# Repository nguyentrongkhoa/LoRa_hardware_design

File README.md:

# 🌍 Overview

This is a 4-layer RF-LoRa-PCB design for my bachelor thesis. The design entails:

1. LoRa transceiver embedded within the STM32WL55 microcontroller
2. BMV080 sensor and BME680 breakout board from Bosch
3. L80-R GPS module from Quectel to test radio coverage
4. SPV1050 solar energy harvesting module
5. BQ24074 battery charging module with USB-C connector

<table>
  <tr>
    <td></td>
    <td></td>
  </tr>
</table>

<details>
<summary><h1>📋STM32WL55CCU6 pinout configuration</h1>  </summary>

|**Pin number** | **Pin name**| **Description**|
|---------------|--------------------|-----------|
|PA0|Blinky LED|To quick test if flashing works
|PA2|VCP_TX|STLinkV3 virtual com port|
|PA3|VCP_RX|STLinkV3 virtual com port|
|PA4|NSS1|SPI1 slave select|
|PA5|SCK1|SPI1 clock signal|
|PA6|MISO1|SPI1|
|PA7|MOSI1|SPI1|
|PA8|MCO|Hook up to oscilloscope to test TCXO 32MHz output|
|PA9 |TX1|UART to communicate with GPS 
|PA10|RX1|UART to communicate with GPS 
|PA12|GPS_RESET|
|PA13|SWDIO|for flashing/debugging
|PA14|SWDCK|for flashing/debugging
|PB2|ALRT|From MAX17048 fuel gauge when battery is low
|PB3|SWO|for flashing/debugging
|PB6|SCL1|I2C to communicate with gas sensors and fuel gauge
|PB7|SDA1|I2C to communicate with gas sensors and fuel gauge
|PB8 |RF_SW_V2| RF switch control input 2 (to choose between receive and transmit)
|PB12|RF_SW_V1| RF switch control input 1
</details>

<details>
  
<summary><h1>🔌Testpoints setup</h1> </summary>

|**Testpoint name** | **Description**| **Expected result**
|---------------|--------------------|----------|
|VBUS|USB voltage|5V when USB is connected
|OUT|output of BQ24074 battery charging module|4.2V when battery is full, ~3.5V when battery empty
|ALRT|MAX17048 fuel gauge alert signal when battery is low|3.3V when battery is full, 0V when empty 

</details>

<details>
<summary><h1>🔍PCB inspection result</h1></summary>
  
## Detailed testing
### Visual inspection
### Electrical tests

#### Power consumption 

</details>

<details>
<summary><h1>✅<b>TODOs for next version</b></h1></summary>

- [ ] Replace SMA connector from Samtec with a cheaper one (see notes in schematic)
- [ ] Tune the antenna side matching network with NanoVNA
- [ ] Remove GPS module since TTFF (time-to-first-fix) is too long
- [ ] Move BMV080 away from MCU
- [ ] Fix VCP (virtual COM port) connections so that debug prints can be displayed in the host comp's terminal
- [ ] Fix PCB edge cut so that it's rectangular and not jagged
- [ ] Fix BMV080 orientation (so that it does not overlap solar cell)
- [ ] Remove USB charging (including BQ24072 charging IC), since the 3.3V LDO of the SPV1050 with max 200 mA can supply the       whole system

</details>

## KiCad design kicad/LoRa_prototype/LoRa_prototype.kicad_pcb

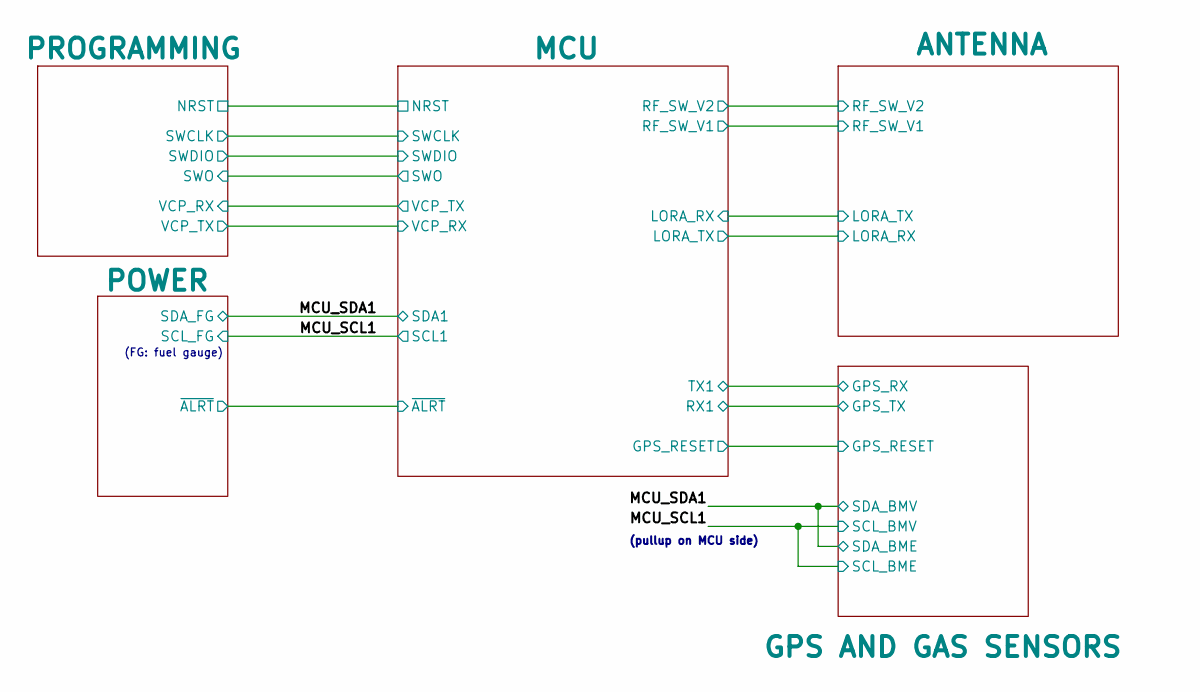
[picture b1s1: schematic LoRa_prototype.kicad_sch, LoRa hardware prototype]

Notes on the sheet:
(FG: fuel gauge)
(pullup on MCU side)

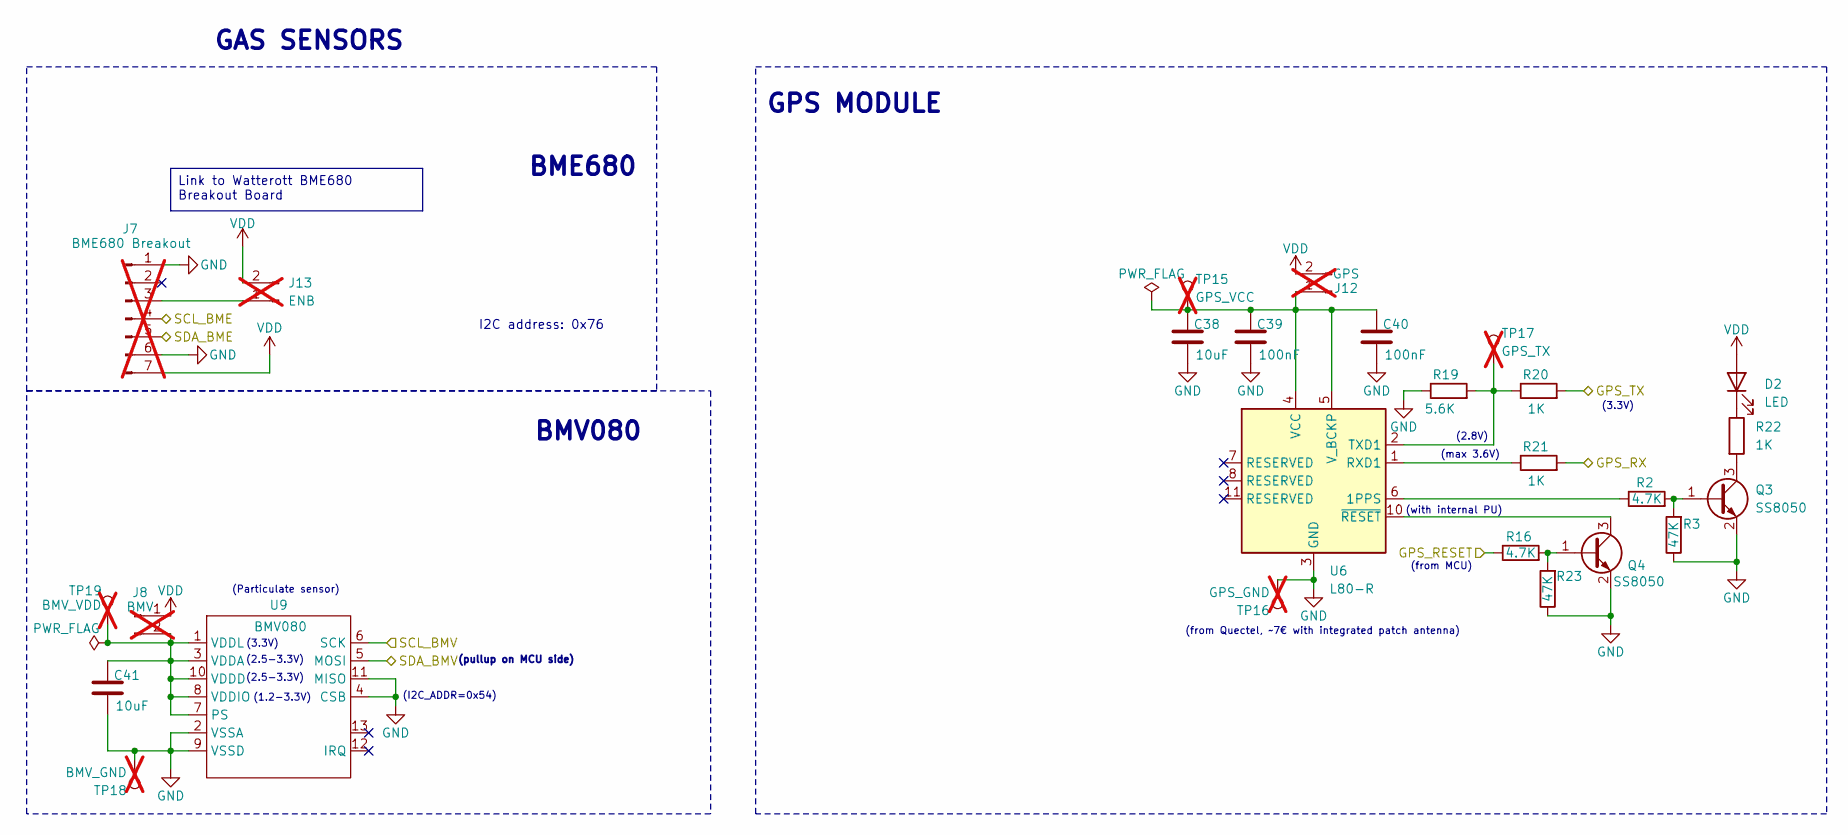
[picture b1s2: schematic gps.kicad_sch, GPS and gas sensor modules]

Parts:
C38, C41: 10uF; C_0603_1608Metric
C39: 100nF; C_0402_1005Metric
C40: 100nF; C_0603_1608Metric
D2: LED; LED_0805_2012Metric
J7: BME680 Breakout; PinSocket_1x07_P2.54mm_Vertical; not fitted
J8: BMV; PinHeader_1x02_P2.54mm_Vertical; not fitted
J12: GPS; PinHeader_1x02_P2.54mm_Vertical; not fitted
J13: ENB; PinHeader_1x02_P2.54mm_Vertical; not fitted
Q3, Q4: SS8050; SOT-23
R2, R16: 4.7K; R_0805_2012Metric
R3, R23: 47K; R_0805_2012Metric
R19: 5.6K; R_0805_2012Metric
R20, R21, R22: 1K; R_0805_2012Metric
TP15: GPS_VCC; TestPoint_Pad_2.0x2.0mm; not fitted
TP16: GPS_GND; TestPoint_Pad_2.0x2.0mm; not fitted
TP17: GPS_TX; TestPoint_Pad_2.0x2.0mm; not fitted
TP18: BMV_GND; TestPoint_Pad_2.0x2.0mm; not fitted
TP19: BMV_VDD; TestPoint_Pad_2.0x2.0mm; not fitted
U6: L80-R; Quectel_L80-R
U9: BMV080; CON_5035661302_MOL; LCSC C587979

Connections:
/GPS AND GAS SENSORS/GPS_RESET: R16.1; also elsewhere on the board
/MCU/RX1: R20.2; also elsewhere on the board
/MCU/TX1: R21.2; also elsewhere on the board
/MCU_SCL1: J7.4, U9.6 (SCK); also elsewhere on the board
/MCU_SDA1: J7.5, U9.5 (MOSI); also elsewhere on the board
GND: C38.2, C39.2, C40.2, C41.2, J7.1, J7.6, Q3.2 (E), Q4.2 (E), R3.1, R19.1, R23.1, TP16.1 (1_1), TP18.1 (1_1), U6.3 (GND), U6.12 (GND), U9.2 (VSSA), U9.4 (CSB), U9.9 (VSSD), U9.11 (MISO); also elsewhere on the board
unnamed: D2.1 (K), R22.1
unnamed: C41.1, J8.2, TP19.1 (1_1), U9.1 (VDDL), U9.3 (VDDA), U9.7 (PS), U9.8 (VDDIO), U9.10 (VDDD)
unnamed: C38.1, C39.1, C40.1, J12.1, TP15.1 (1_1), U6.4 (VCC), U6.5 (V_BCKP)
unnamed: J7.3, J13.1
unnamed: Q3.1 (B), R2.2, R3.2
unnamed: Q3.3 (C), R22.2
unnamed: Q4.1 (B), R16.2, R23.2
unnamed: Q4.3 (C), U6.10 (~RESET)
unnamed: R2.1, U6.6 (1PPS)
unnamed: R21.1, U6.1 (RXD1)
unnamed: R19.2, R20.1, TP17.1 (1_1), U6.2 (TXD1)
VDD: D2.2 (A), J7.7, J8.1, J12.2, J13.2; also elsewhere on the board

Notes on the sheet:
BME680
(from MCU)
BMV080
(max 3.6V)
(with internal PU)
(I2C_ADDR=0x54)
(2.8V)
(from Quectel, ~7€ with integrated patch antenna)
GPS MODULE
(Particulate sensor)
GAS SENSORS
(3.3V)
(pullup on MCU side)
(2.5-3.3V)
I2C address: 0x76
(1.2-3.3V)
Link to Watterott BME680 Breakout Board

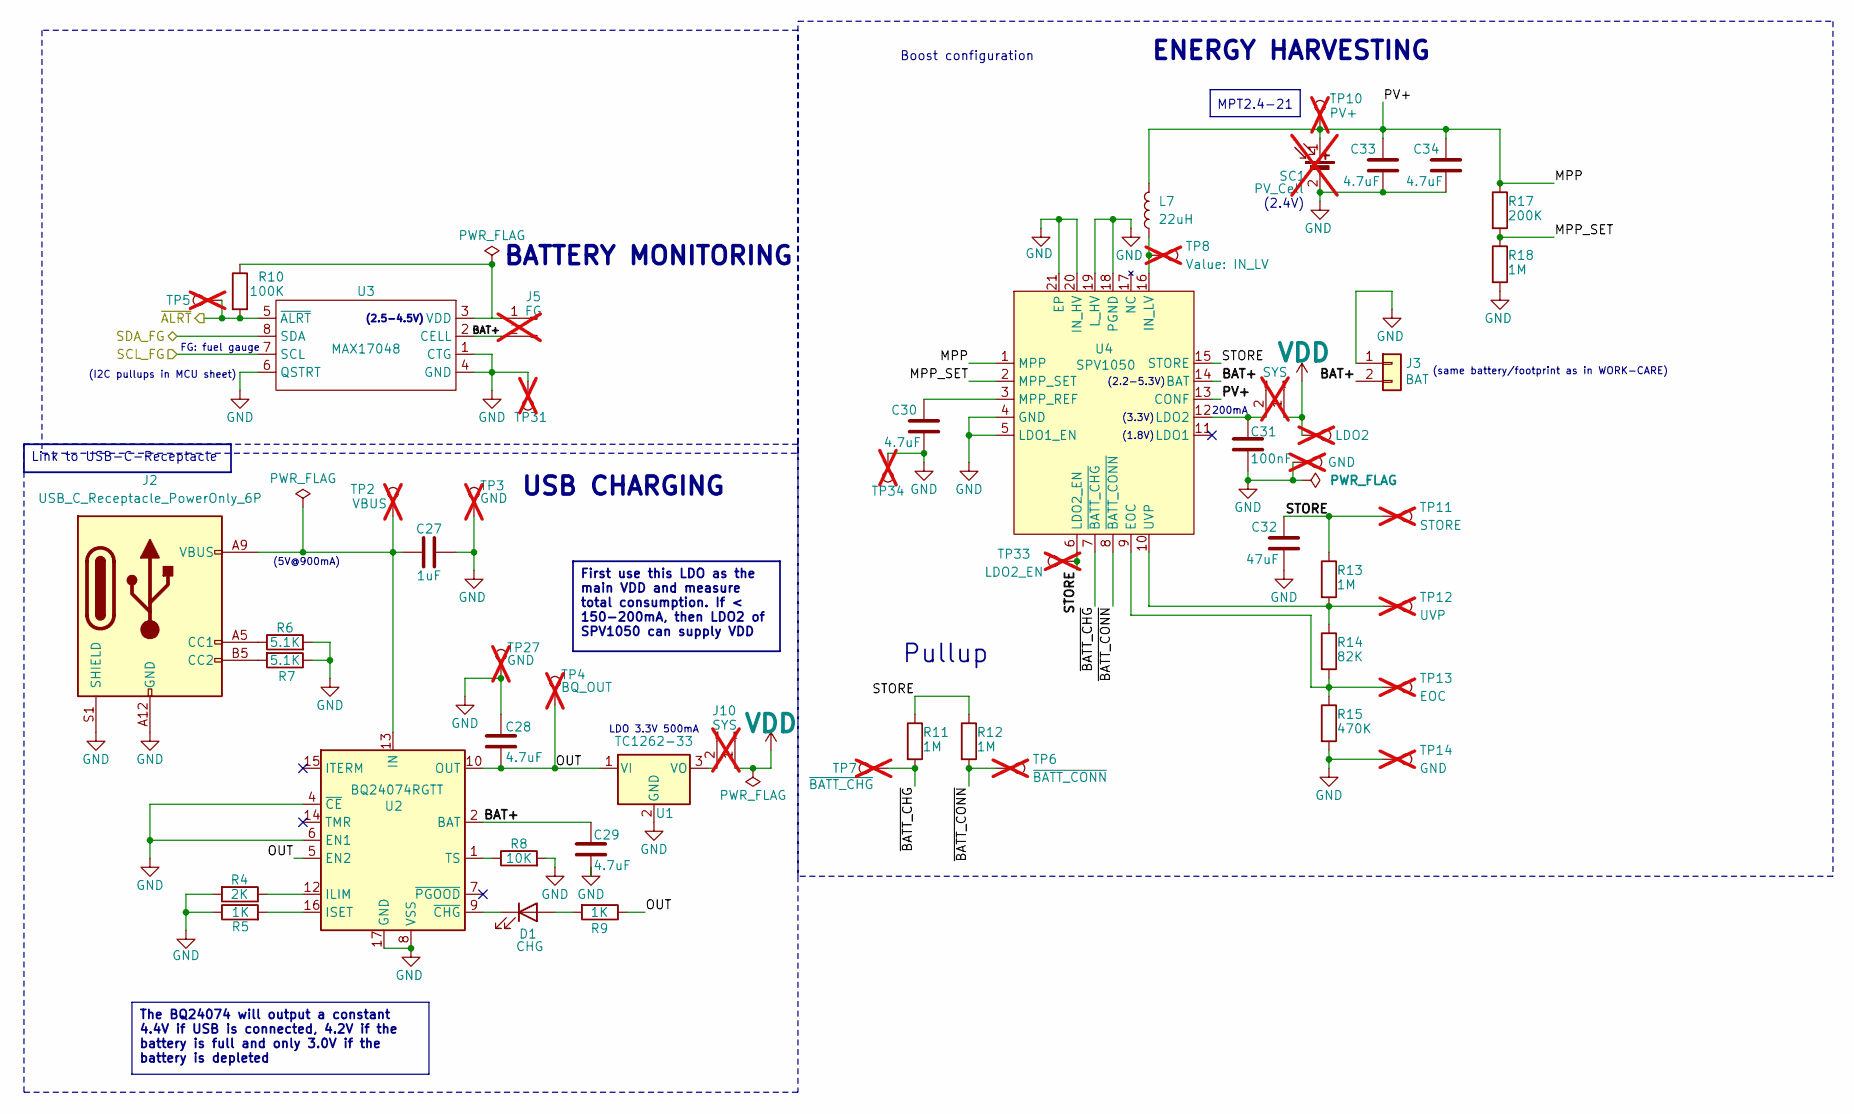
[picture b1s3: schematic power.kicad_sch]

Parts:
C27: 1uF; C_0603_1608Metric; LCSC C1592
C28, C29: 4.7uF; C_0603_1608Metric; LCSC C19666
C30, C33, C34: 4.7uF; C_0603_1608Metric
C31: 100nF; C_0402_1005Metric
C32: 47uF; C_0805_2012Metric
D1: CHG; LED_0805_2012Metric; LCSC C94740
J2: USB_C_Receptacle_PowerOnly_6P; UC17-0B06F68011
J3: BAT; JST_GH_SM02B-GHS-TB_1x02-1MP_P1.25mm_Horizontal; LCSC C189893
J5: FG; PinHeader_1x02_P2.54mm_Vertical; not fitted
J10, J15: SYS; PinHeader_1x02_P2.54mm_Vertical; not fitted
L7: 22uH; PSPMAA0402-220M-ANP
R4: 2K; R_0805_2012Metric; LCSC C4177
R5: 1K; R_0805_2012Metric; LCSC C21190
R6, R7: 5.1K; R_0805_2012Metric
R8: 10K; R_0805_2012Metric; LCSC C25804
R9: 1K; R_0805_2012Metric; LCSC C20686
R10: 100K; R_0805_2012Metric
R11, R12, R13, R18: 1M; R_0805_2012Metric
R14: 82K; R_0603_1608Metric
R15: 470K; R_0805_2012Metric
R17: 200K; R_0805_2012Metric
SC1: PV_Cell; MPT2.4-21; not fitted
TP2: VBUS; TestPoint_Pad_2.0x2.0mm; not fitted
TP3, TP14, TP27, TP28, TP31, TP34: GND; TestPoint_Pad_2.0x2.0mm; not fitted
TP4: BQ_OUT; TestPoint_Pad_2.0x2.0mm; not fitted
TP5: ~{ALRT}; TestPoint_Pad_2.0x2.0mm; not fitted
TP6: ~{BATT_CONN}; TestPoint_Pad_2.0x2.0mm; not fitted
TP7: ~{BATT_CHG}; TestPoint_Pad_2.0x2.0mm; not fitted
TP8: IN_LV; TestPoint_Pad_2.0x2.0mm; not fitted
TP9: LDO2; TestPoint_Pad_2.0x2.0mm; not fitted
TP10: PV+; TestPoint_Pad_2.0x2.0mm; not fitted
TP11: STORE; TestPoint_Pad_2.0x2.0mm; not fitted
TP12: UVP; TestPoint_Pad_2.0x2.0mm; not fitted
TP13: EOC; TestPoint_Pad_2.0x2.0mm; not fitted
TP33: LDO2_EN; TestPoint_Pad_2.0x2.0mm; not fitted
U1: TC1262-33; SOT-223-3
U2: BQ24074RGTT; VQFN-16-1EP_3x3mm_P0.5mm_EP1.6x1.6mm; LCSC C54313
U3: MAX17048; SON50P200X200X80-9N
U4: SPV1050; QFN40P300X300X100-21N

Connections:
/MCU/~ALRT: R10.2, TP5.1 (1_1), U3.5 (~ALRT); also elsewhere on the board
/MCU_SCL1: U3.7 (SCL); also elsewhere on the board
/MCU_SDA1: U3.8 (SDA); also elsewhere on the board
/POWER/BAT+: C29.2, J3.2, J5.2, U2.2 (BAT), U2.3 (BAT), U3.2 (CELL), U4.14 (BAT)
/POWER/MPP: C33.2, C34.2, L7.2, R17.1, SC1.1 (+), TP10.1 (1_1), U4.1 (MPP), U4.13 (CONF)
/POWER/MPP_SET: R17.2, R18.1, U4.2 (MPP_SET)
/POWER/OUT: C28.1, R9.1, TP4.1 (1_1), U1.1 (VI), U2.5 (EN2), U2.10 (OUT), U2.11 (OUT)
/POWER/STORE: C32.2, R11.1, R12.1, R13.1, TP11.1 (1_1), TP33.1 (1_1), U4.6 (LDO2_EN), U4.15 (STORE); also elsewhere on the board
/POWER/~BATT_CHG: R11.2, TP7.1 (1_1), U4.7 (~BATT_CHG)
/POWER/~BATT_CONN: R12.2, TP6.1 (1_1), U4.8 (~BATT_CONN)
GND: C27.2, C28.2, C29.1, C30.1, C31.2, C32.1, C33.1, C34.1, J2.A12 (GND), J2.B12 (GND), J2.S1 (SHIELD), J3.1, R4.2, R5.1, R6.2, R7.1, R8.2, R15.2, R18.2, SC1.2 (-), TP3.1 (1_1), TP14.1 (1_1), TP27.1 (1_1), TP28.1 (1_1), TP31.1 (1_1), TP34.1 (1_1), U1.2 (GND), U2.4 (~CE), U2.6 (EN1), U2.8 (VSS), U2.17 (GND), U3.1 (CTG), U3.4 (GND), U3.6 (QSTRT), U4.4 (GND), U4.5 (LDO1_EN), U4.18 (PGND), U4.19 (L_HV), U4.20 (IN_HV), U4.21 (EP); also elsewhere on the board
unnamed: D1.2 (A), R9.2
unnamed: D1.1 (K), U2.9 (~CHG)
unnamed: J2.A5 (CC1), R6.1
unnamed: J2.B5 (CC2), R7.2
unnamed: J5.1, R10.1, U3.3 (VDD)
unnamed: J10.2, U1.3 (VO)
unnamed: C31.1, J15.2, U4.12 (LDO2)
unnamed: R4.1, U2.12 (ILIM)
unnamed: C27.1, J2.A9 (VBUS), J2.B9 (VBUS), TP2.1 (1_1), U2.13 (IN)
unnamed: R5.2, U2.16 (ISET)
unnamed: R8.1, U2.1 (TS)
unnamed: R14.2, R15.1, TP13.1 (1_1), U4.9 (EOC)
unnamed: L7.1, TP8.1 (1_1), U4.16 (IN_LV)
unnamed: C30.2, U4.3 (MPP_REF)
unnamed: R13.2, R14.1, TP12.1 (1_1), U4.10 (UVP)
VDD: J10.1, J15.1, TP9.1 (1_1); also elsewhere on the board

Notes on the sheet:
Boost configuration
(5V@900mA)
ENERGY HARVESTING
(2.5-4.5V)
200mA
BATTERY MONITORING
MPT2.4-21
(2.2-5.3V)
FG: fuel gauge
(3.3V)
LDO 3.3V 500mA
Pullup
USB CHARGING
(same battery/footprint as in WORK-CARE)
(2.4V)
(I2C pullups in MCU sheet)
(1.8V)
Link to USB-C-Receptacle
First use this LDO as the main VDD and measure total consumption. If < 150-200mA, then LDO2 of SPV1050 can supply VDD
The BQ24074 will output a constant 4.4V if USB is connected, 4.2V if the battery is full and only 3.0V if the battery is depleted

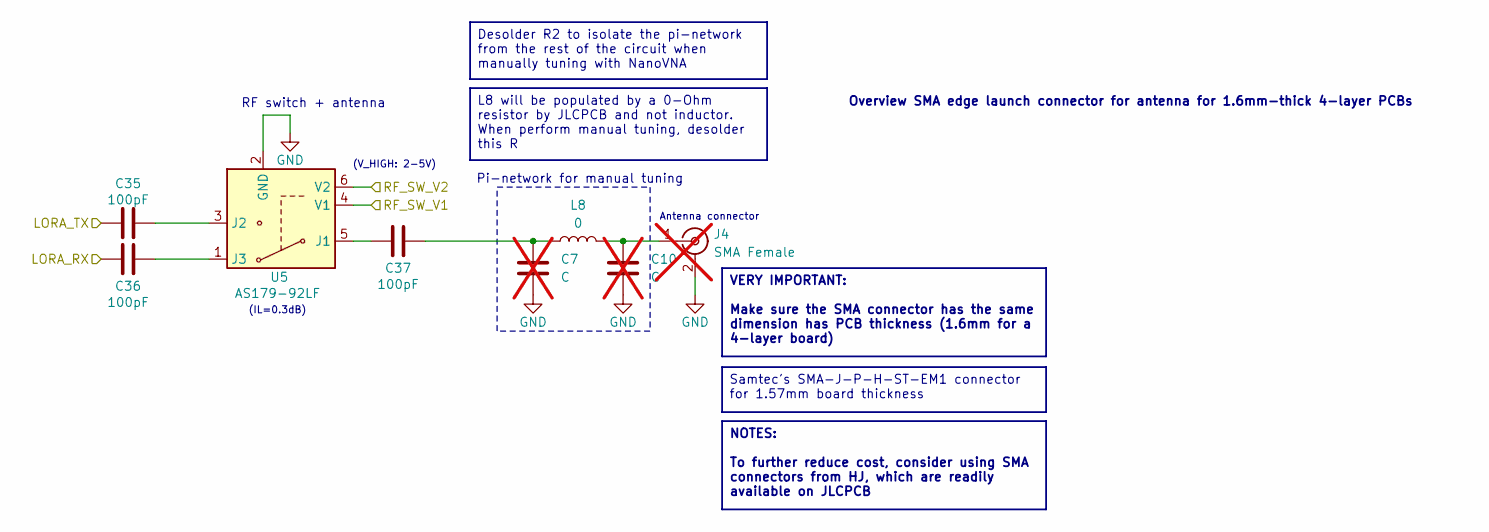
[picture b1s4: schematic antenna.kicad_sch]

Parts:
C7, C10: C; C_0603_1608Metric; not fitted
C35, C36, C37: 100pF; C_0402_1005Metric
J4: SMA Female; SMA_Samtec_SMA-J-P-H-ST-EM1_EdgeMount; LCSC C5137195; not fitted
L8: 0; L_0603_1608Metric
U5: AS179-92LF; SOT-363_SC-70-6

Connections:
/ANTENNA/LORA_RX: C36.1; also elsewhere on the board
/ANTENNA/LORA_TX: C35.1; also elsewhere on the board
/ANTENNA/RF_SW_V1: U5.4 (V1); also elsewhere on the board
/ANTENNA/RF_SW_V2: U5.6 (V2); also elsewhere on the board
GND: C7.2, C10.2, J4.2 (Ext), U5.2 (GND); also elsewhere on the board
unnamed: C7.1, C37.2, L8.1
unnamed: C10.1, J4.1 (In), L8.2
unnamed: C37.1, U5.5 (J1)
unnamed: C35.2, U5.3 (J2)
unnamed: C36.2, U5.1 (J3)

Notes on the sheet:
(V_HIGH: 2-5V)
Pi-network for manual tuning
RF switch + antenna
(IL=0.3dB)
Antenna connector
Overview SMA edge launch connector for antenna for 1.6mm-thick 4-layer PCBs
Samtec's SMA-J-P-H-ST-EM1 connector for 1.57mm board thickness
Desolder R2 to isolate the pi-network from the rest of the circuit when manually tuning with NanoVNA
L8 will be populated by a 0-Ohm resistor by JLCPCB and not inductor. When perform manual tuning, desolder this R
VERY IMPORTANT: Make sure the SMA connector has the same dimension has PCB thickness (1.6mm for a 4-layer board)
NOTES: To further reduce cost, consider using SMA connectors from HJ, which are readily available on JLCPCB

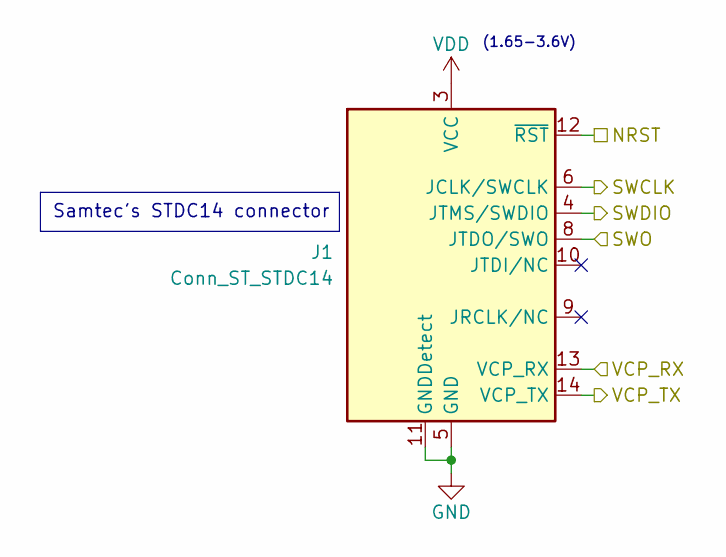
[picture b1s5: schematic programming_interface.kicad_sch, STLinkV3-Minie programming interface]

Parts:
J1: Conn_ST_STDC14; PinHeader_2x07_P1.27mm_Vertical

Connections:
/MCU/NRST: J1.12 (~RST); also elsewhere on the board
/MCU/SWCLK: J1.6 (JCLK/SWCLK); also elsewhere on the board
/MCU/SWDIO: J1.4 (JTMS/SWDIO); also elsewhere on the board
/MCU/SWO: J1.8 (JTDO/SWO); also elsewhere on the board
/MCU/VCP_RX: J1.14 (VCP_TX); also elsewhere on the board
/MCU/VCP_TX: J1.13 (VCP_RX); also elsewhere on the board
GND: J1.5 (GND), J1.7 (GND), J1.11 (GNDDetect); also elsewhere on the board
VDD: J1.3 (VCC); also elsewhere on the board

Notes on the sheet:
Samtec's STDC14 connector
(1.65-3.6V)

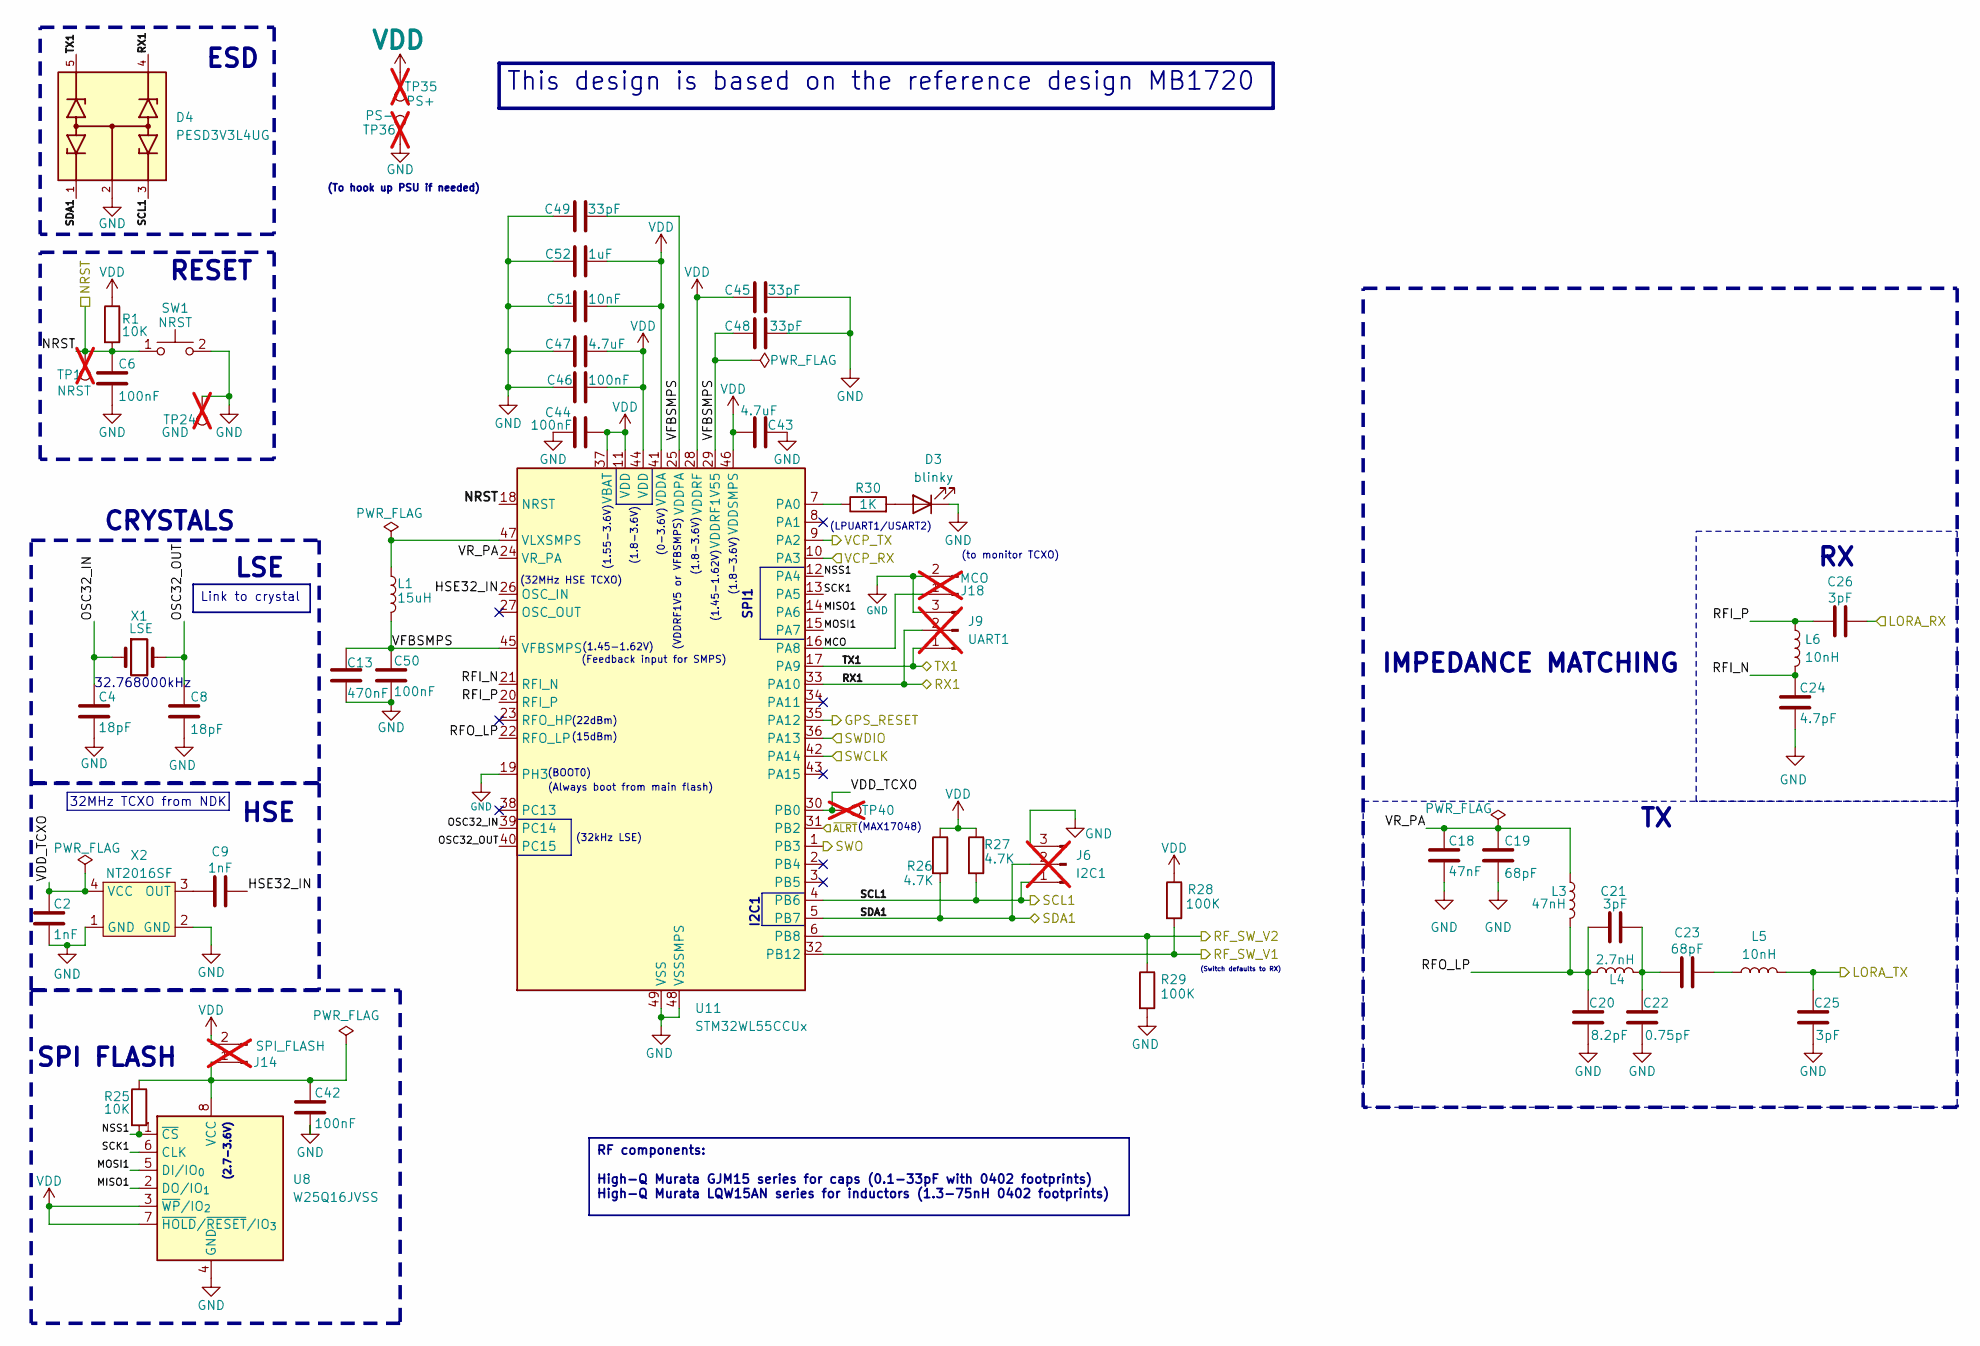
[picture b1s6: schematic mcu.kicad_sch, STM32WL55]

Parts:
C2, C9: 1nF; C_0402_1005Metric
C4, C8: 18pF; C_0402_1005Metric
C6, C42, C44, C46, C50: 100nF; C_0402_1005Metric
C13: 470nF; C_0603_1608Metric
C18: 47nF; C_0603_1608Metric
C19, C23: 68pF; C_0402_1005Metric
C20: 8.2pF; C_0402_1005Metric
C21, C25, C26: 3pF; C_0402_1005Metric
C22: 0.75pF; C_0402_1005Metric
C24: 4.7pF; C_0402_1005Metric
C43, C47: 4.7uF; C_0402_1005Metric
C45, C48, C49: 33pF; C_0402_1005Metric
C51: 10nF; C_0402_1005Metric
C52: 1uF; C_0402_1005Metric
D3: blinky; LED_0805_2012Metric
D4: PESD3V3L4UG; DIO_PESD3V3L4UG; PARTREV 04
J6: I2C1; PinHeader_1x03_P2.54mm_Vertical; not fitted
J9: UART1; PinHeader_1x03_P2.54mm_Vertical; not fitted
J14: SPI_FLASH; PinHeader_1x02_P2.54mm_Vertical; not fitted
J18: MCO; PinHeader_1x02_P2.54mm_Vertical; not fitted
L1: 15uH; L_0402_1005Metric
L3: 47nH; L_0402_1005Metric
L4: 2.7nH; L_0402_1005Metric
L5, L6: 10nH; L_0402_1005Metric
R1: 10K; R_0603_1608Metric
R25: 10K; R_0805_2012Metric
R26, R27: 4.7K; R_0603_1608Metric
R28, R29: 100K; R_0603_1608Metric
R30: 1K; R_0603_1608Metric
SW1: NRST; TS-1088-AR02016
TP1: NRST; TestPoint_Pad_2.0x2.0mm; not fitted
TP24: GND; TestPoint_Pad_2.0x2.0mm; not fitted
TP35: PS+; TestPoint_THTPad_2.0x2.0mm_Drill1.0mm; not fitted
TP36: PS-; TestPoint_THTPad_2.0x2.0mm_Drill1.0mm; not fitted
TP40: VDDXO; TestPoint_Pad_2.0x2.0mm; not fitted
U8: W25Q16JVSS; SOIC-8_5.3x5.3mm_P1.27mm
U11: STM32WL55CCUx; QFN-48-1EP_7x7mm_P0.5mm_EP5.6x5.6mm
X1: LSE; Crystal_SMD_3215-2Pin_3.2x1.5mm
X2: NT2016SF; NT2016SF TCXO

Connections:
/ANTENNA/LORA_RX: C25.1, L5.2; also elsewhere on the board
/ANTENNA/LORA_TX: C26.2; also elsewhere on the board
/ANTENNA/RF_SW_V1: R28.2, U11.32 (PB12); also elsewhere on the board
/ANTENNA/RF_SW_V2: R29.1, U11.6 (PB8); also elsewhere on the board
/GPS AND GAS SENSORS/GPS_RESET: U11.35 (PA12); also elsewhere on the board
/MCU/HSE32_IN: C9.2, U11.26 (OSC_IN)
/MCU/MCO: J18.1, U11.16 (PA8)
/MCU/MISO1: U8.2 (DO/IO_{1}), U11.14 (PA6)
/MCU/MOSI1: U8.5 (DI/IO_{0}), U11.15 (PA7)
/MCU/NRST: C6.1, R1.2, SW1.1, TP1.1 (1_1), U11.18 (NRST); also elsewhere on the board
/MCU/NSS1: R25.2, U8.1 (~CS), U11.12 (PA4)
/MCU/OSC32_IN: C4.1, U11.39 (PC14), X1.1
/MCU/OSC32_OUT: C8.1, U11.40 (PC15), X1.2
/MCU/RFI_N: C24.1, L6.2, U11.21 (RFI_N)
/MCU/RFI_P: C26.1, L6.1, U11.20 (RFI_P)
/MCU/RFO_LP: C20.1, C21.1, L3.2, L4.1, U11.22 (RFO_LP)
/MCU/RX1: D4.4, J9.2, U11.33 (PA10); also elsewhere on the board
/MCU/SCK1: U8.6 (CLK), U11.13 (PA5)
/MCU/SWCLK: U11.42 (PA14); also elsewhere on the board
/MCU/SWDIO: U11.36 (PA13); also elsewhere on the board
/MCU/SWO: U11.1 (PB3); also elsewhere on the board
/MCU/TX1: D4.5, J9.1, U11.17 (PA9); also elsewhere on the board
/MCU/VCP_RX: U11.10 (PA3); also elsewhere on the board
/MCU/VCP_TX: U11.9 (PA2); also elsewhere on the board
/MCU/VDD_TCXO: C2.1, TP40.1 (1_1), U11.30 (PB0), X2.4 (VCC)
/MCU/VFBSMPS: C13.1, C48.1, C49.2, C50.1, L1.2, U11.25 (VDDPA), U11.29 (VDDRF1V55), U11.45 (VFBSMPS)
/MCU/VR_PA: C18.1, C19.1, L3.1, U11.24 (VR_PA)
/MCU/~ALRT: U11.31 (PB2); also elsewhere on the board
/MCU_SCL1: D4.3, J6.1, R27.2, U11.4 (PB6); also elsewhere on the board
/MCU_SDA1: D4.1, J6.2, R26.2, U11.5 (PB7); also elsewhere on the board
GND: C2.2, C4.2, C6.2, C8.2, C13.2, C18.2, C19.2, C20.2, C22.2, C24.2, C25.2, C42.2, C43.2, C44.2, C45.2, C46.2, C47.2, C48.2, C49.1, C50.2, C51.2, C52.2, D3.1 (K), D4.2, J6.3, J9.3, J18.2, R29.2, SW1.2, TP24.1 (1_1), TP36.1 (1_1), U8.4 (GND), U11.19 (PH3), U11.48 (VSSSMPS), U11.49 (VSS), X2.1 (GND), X2.2 (GND); also elsewhere on the board
unnamed: C21.2, C22.1, C23.1, L4.2
unnamed: C23.2, L5.1
unnamed: D3.2 (A), R30.2
unnamed: C42.1, J14.1, R25.1, U8.8 (VCC)
unnamed: R30.1, U11.7 (PA0)
unnamed: L1.1, U11.47 (VLXSMPS)
unnamed: C9.1, X2.3 (OUT)
VDD: C43.1, C44.1, C45.1, C46.1, C47.1, C51.1, C52.1, J14.2, R1.1, R26.1, R27.1, R28.1, TP35.1 (1_1), U8.3 (~WP/IO_{2}), U8.7 (~HOLD/~RESET/IO_{3}), U11.11 (VDD), U11.28 (VDDRF), U11.37 (VBAT), U11.41 (VDDA), U11.44 (VDD), U11.46 (VDDSMPS); also elsewhere on the board

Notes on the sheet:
SPI FLASH
RESET
IMPEDANCE MATCHING
(1.45-1.62V)
(To hook up PSU if needed)
(LPUART1/USART2)
(1.8-3.6V)
(BOOT0)
(Feedback input for SMPS)
I2C1
(0-3.6V)
(32kHz LSE)
(MAX17048)
CRYSTALS
(Switch defaults to RX)
LSE
(15dBm)
(2.7-3.6V)
32MHz TCXO from NDK
SPI1
(32MHz HSE TCXO)
ESD
(1.55-3.6V)
HSE
(to monitor TCXO)
(22dBm)
(VDDRF1V5 or VFBSMPS)
32.768000kHz
(Always boot from main flash)
RF components: High-Q Murata GJM15 series for caps (0.1-33pF with 0402 footprints) High-Q Murata LQW15AN series for inductors (1.3-75nH 0402 footprints)
This design is based on the reference design MB1720
Link to crystal

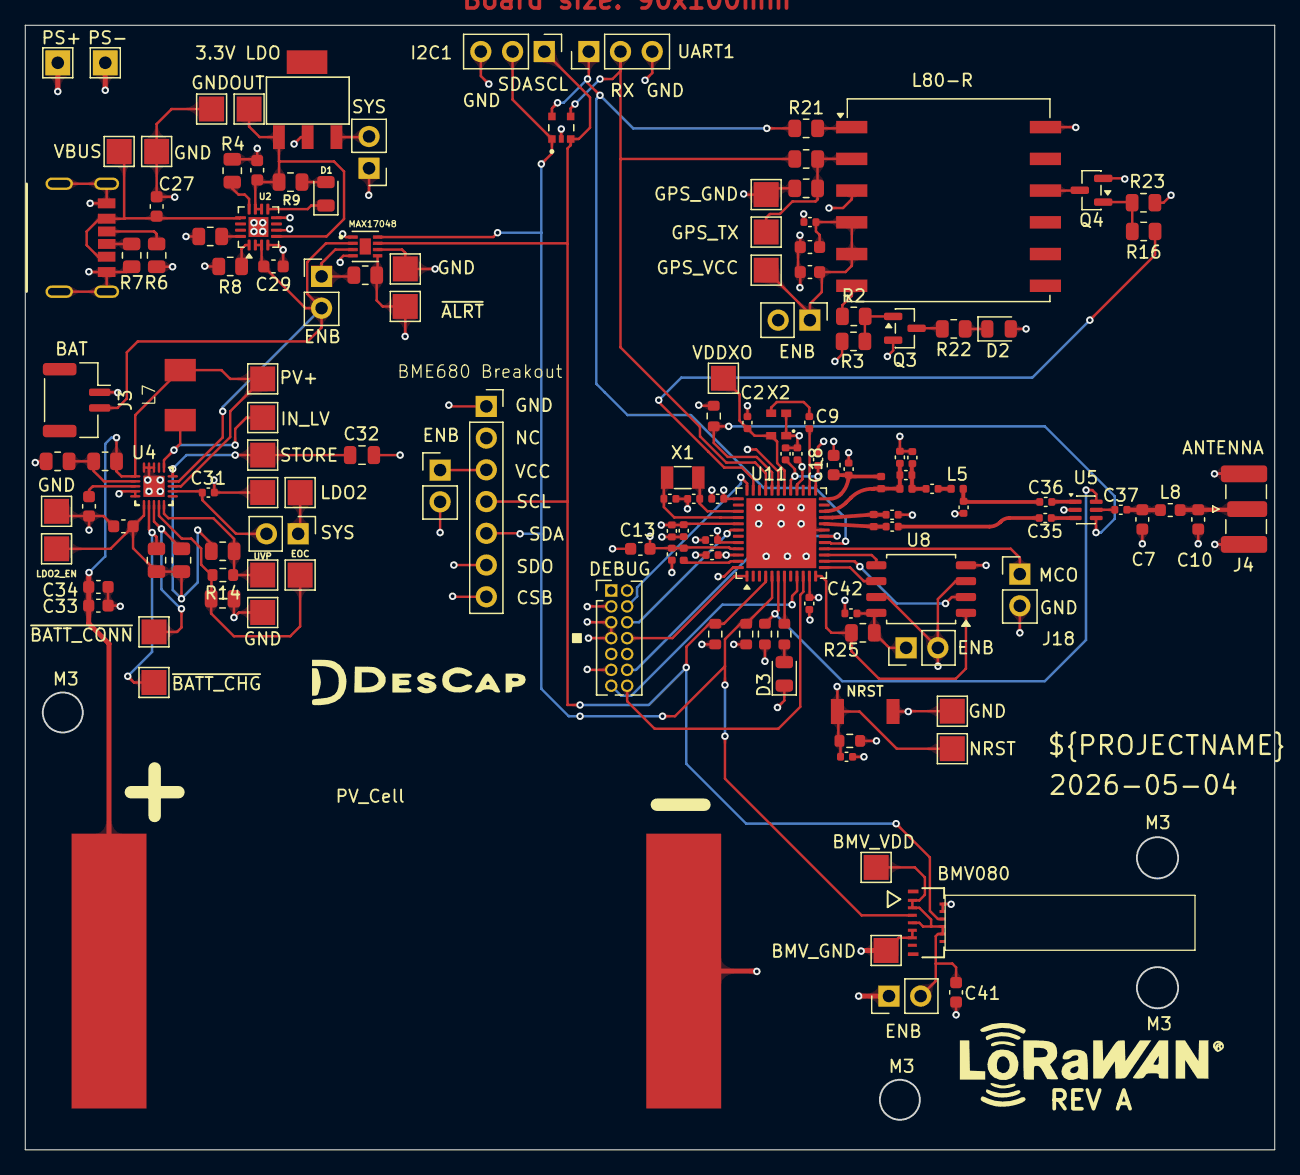
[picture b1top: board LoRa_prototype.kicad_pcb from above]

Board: 4 copper layers, 99.9 x 89.9 mm, 142 parts (0 on the bottom side), 77 nets.

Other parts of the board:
C32#2: 47uF; C_0805_2012Metric

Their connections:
/POWER/STORE: C32#2.2; also elsewhere on the board
GND: C32#2.1; also elsewhere on the board

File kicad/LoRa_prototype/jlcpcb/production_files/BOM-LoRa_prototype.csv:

Comment,Designator,Footprint,LCSC,Quantity
0,L8,L_0603_1608Metric,C21189,1
0.75pF,C22,C_0402_1005Metric,C2931057,1
1.5M,R17,R_0805_2012Metric,C26110,1
1.8K,R4,R_0805_2012Metric,C17420,1
100K,R10,R_0805_2012Metric,C149504,1
100K,"R28,R29",R_0603_1608Metric,C25803,2
100nF,C40,C_0603_1608Metric,C14663,1
100nF,"C31,C39,C42,C44,C46,C50,C6",C_0402_1005Metric,C1525,7
100pF,"C35,C36,C37",C_0402_1005Metric,C77177,3
10K,"R25,R8",R_0805_2012Metric,C17414,2
10K,R1,R_0603_1608Metric,C25804,1
10M,"R11,R12",R_0805_2012Metric,C101929,2
10nF,C51,C_0402_1005Metric,C15195,1
10nH,"L5,L6",L_0402_1005Metric,C184029,2
10uF,"C38,C41",C_0603_1608Metric,C19702,2
15uH,L1,L_0402_1005Metric,C3221788,1
18pF,"C4,C8",C_0402_1005Metric,C1549,2
1K,"R20,R21,R22,R5,R9",R_0805_2012Metric,C17513,5
1K,R30,R_0603_1608Metric,C21190,1
1nF,"C2,C9",C_0402_1005Metric,C1523,2
1uF,C27,C_0603_1608Metric,C15849,1
1uF,C52,C_0402_1005Metric,C52923,1
2.7M,R15,R_0805_2012Metric,C170861,1
2.7nH,L4,L_0402_1005Metric,C91239,1
22uH,L7,L_0402_1005Metric,C5273842,1
3.6nH,L2,L_0402_1005Metric,C408158,1
33pF,"C45,C48,C49",C_0402_1005Metric,C76905,3
3pF,"C21,C25,C26",C_0402_1005Metric,C76906,3
4.7K,"R26,R27",R_0603_1608Metric,C23162,2
4.7pF,C24,C_0402_1005Metric,C85883,1
4.7uF,"C28,C29,C30,C33,C34",C_0603_1608Metric,C1705,5
4.7uF,"C43,C47",C_0402_1005Metric,C23733,2
470nF,C13,C_0402_1005Metric,C77003,1
47nF,C18,C_0402_1005Metric,C77017,1
47nH,L3,L_0402_1005Metric,C22334,1
47uF,C32,C_0603_1608Metric,C140782,1
5.1K,"R6,R7",R_0805_2012Metric,C27834,2
5.6K,R19,R_0805_2012Metric,C4382,1
500K,R14,R_0805_2012Metric,C3097783,1
6.2M,R13,R_0805_2012Metric,C63172,1
68pF,"C19,C23",C_0402_1005Metric,C76977,2
8.2M,R18,R_0805_2012Metric,C17829,1
8.2pF,C20,C_0402_1005Metric,C88898,1
AS179-92LF,U5,SOT-363_SC-70-6,C83422,1
BAT,J3,JST_GH_SM02B-GHS-TB_1x02-1MP_P1.25mm_Horizontal,C189893,1
BME,J11,PinHeader_1x02_P2.54mm_Vertical,C53207323,1
BME688,U7,IC_BME688,C3664478,1
BMV,J8,PinHeader_1x02_P2.54mm_Vertical,C53207323,1
BMV080,U9,CON_5035661302_MOL,C587979,1
BQ24074RGTT,U2,VQFN-16-1EP_3x3mm_P0.5mm_EP1.6x1.6mm,C54313,1
CHG,D1,LED_0805_2012Metric,C94740,1
Conn_ST_STDC14,J1,PinHeader_2x07_P1.27mm_Vertical,C3333025,1
DTC143Z,"Q1,Q2",SOTFL50P160X85-3N,C308696,2
FG,J5,PinHeader_1x02_P2.54mm_Vertical,C53207323,1
GPS,J12,PinHeader_1x02_P2.54mm_Vertical,C53207323,1
I2C1,J6,PinHeader_1x03_P2.54mm_Vertical,C53207325,1
L80-R,U6,Quectel_L80-R,C3029061,1
LED,D2,LED_0805_2012Metric,C2296,1
LSE,X1,Crystal_SMD_3215-2Pin_3.2x1.5mm,C32346,1
MAX17048,U3,SON50P200X200X80-9N,C2682616,1
MCO,J18,PinHeader_1x02_P2.54mm_Vertical,C53207323,1
NRST,SW1,TS-1088-AR02016,C720477,1
NT2016SF,X2,NT2016SF TCXO,C36338880,1
PESD3V3L4UG,D4,DIO_PESD3V3L4UG,C52741412,1
SMA Female,J4,SMA_Samtec_SMA-J-P-H-ST-EM1_EdgeMount,C5137195,1
SPI_FLASH,J14,PinHeader_1x02_P2.54mm_Vertical,C53207323,1
SPV1050,U4,QFN40P300X300X100-21N,C5181469,1
STM32WL55CCUx,U11,QFN-48-1EP_7x7mm_P0.5mm_EP5.6x5.6mm,C5270474,1
SYS,"J10,J15",PinHeader_1x02_P2.54mm_Vertical,C53207323,2
TC1262-33,U1,SOT-223-3,C52507,1
UART1,J9,PinHeader_1x03_P2.54mm_Vertical,C53207325,1
USB_C_Receptacle_PowerOnly_6P,J2,UC17-0B06F68011,C36936554,1
W25Q16JVSS,U8,SOIC-8_5.3x5.3mm_P1.27mm,C131025,1
blinky,D3,LED_0805_2012Metric,C2297,1

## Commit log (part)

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2026-04-05 Added datasheets
2026-04-05 Added first KiCad files (Milestone)
2026-04-05 Added more components datasheets
2026-04-05 Added more component datasheets + JLCPCB preorder (Milestone)
2026-04-06 Added more component datasheets
2026-04-07 Added MB1842 reference designs as resource
2026-04-07 Added MB1849-LP reference design as resource
2026-04-07 Added application notes for STM32WL5x MCUs
2026-04-08 Added more app notes
2026-04-09 Implement power decoupling in schematic
2026-04-13 Added app note for STM32WL
2026-04-13 Added component datasheets
2026-04-13 Done RF matching network in schematic
2026-04-13 Added component datasheet
2026-04-13 Stable commit
2026-04-13 Reorganized schematic
2026-04-13 Added custom TCXO symbol
2026-04-14 Added LSE and HSE crystals to schematic
2026-04-14 Done doing MCU schematic (Milestone)
2026-04-14 Schematic for programming interface done
2026-04-14 Add SPV1050 symbol in schematic
2026-04-15 Added SPV1050 app notes
2026-04-15 Start power management block in schematic
2026-04-16 Done schematic for SPV1050 (Milestone)
2026-04-16 Done power block in schematics + ERC passed with 0 errors
2026-04-17 Added documents for L80 GPS module
2026-04-17 Start schematic for GPS module
2026-04-17 Done schematic GPS block with 0 ERC errors (Milestone)
2026-04-17 Copied and cleaned up USb charging circuit from WORK-CARE
    1 ERC error
2026-04-18 Added I2C pullups for fuel guage
2026-04-18 Added footprints and syms for sensor connectors
2026-04-18 Started adding gas sensors to schematic
2026-04-18 Added footprint and symbol BME688
2026-04-18 Done schematic for GPS and gas sensors (Milestone)
2026-04-18 Schematic cleanup (0 ERC violations)
2026-04-18 Added more testpoints to schematic
2026-04-18 Added footprints SPV1050 & SPI Flash
2026-04-20 Done schematic with 0 ERC errors (Milestone)
    Still need to double/triple check tho
2026-04-20 Prettified schematic
2026-04-20 Added pin headers in schematics
    To activate/deactivate subsystems as well as measure currents
2026-04-21 Created separate folders for footprints and 3d models
2026-04-21 Last note on this branch
    stm32wl55jci6 is not available on JLCPCB
2026-04-21 Redone schematic with stm32wl55ccu6
    The original MCU STM32WL55JCI6 is still left on the schematic so come back here if something is messed up
2026-04-21 Finally removed stm32wl55jci6
2026-04-21 Grouped items in schematic (only Kicad 10+)
2026-04-21 Add .gitignore
2026-04-22 Added ref designs for UQFPN MCU
2026-04-22 Removed redundant I2C test pin headers
2026-04-22 Updated component values to match E24 series
2026-04-22 Added ESD protection to I2C and UART headers
2026-04-23 Added 3.3V 500mA LDO
2026-04-23 Assigned most footprints
2026-04-24 Added more footprints
2026-04-24 Updated datasheets
2026-04-24 Added 3d model of fuel gauge
2026-04-24 Assigned almost all footprints
2026-04-25 Added more footprints and 3d models
2026-04-25 Assigned all footprints
2026-04-25 Added datasheets for potential SMA antenna connectors
2026-04-25 Schematic & footprint assignment done (Milestone)
2026-04-26 Started PCB Layout (Milestone)
2026-04-27 Minor changes
2026-04-27 Routed HSE
2026-04-27 Routed LSE
2026-04-27 Routed USB and charging IC
2026-04-27 Done routing fuel gauge
2026-04-27 Done routing power sheet
2026-04-27 Done routing gas sensors
2026-04-27 Done routing GPS
2026-04-28 Changed decoupling in schematic
2026-04-28 Cleaned up schematic
2026-04-28 Added netclasses to schematic
2026-04-28 Routed 1/2 of MCU and SPI_Flash
2026-04-28 Routed I2C and ESD protection for MCU
2026-04-28 Done routing antenna and RF switch
2026-04-28 Routed programming interface
2026-04-29 Added KiNotes to project
2026-05-01 90% done (before ground and power pour)
2026-05-01 Added thermal vias to all ICs
2026-05-01 Connected all items (with 56 DRC violations)
2026-05-02 Stable commit (only 11 DRC violations now)
2026-05-02 Stable commit (0 DRC violations 267 warnings)
2026-05-02 Adjusted some silkscreen texts (now down to 86 DRC)
2026-05-03 Prettified silkscreen layer
    0 errors and 33 warnings in DRC
2026-05-03 Done layout (Milestone)
2026-05-03 Added part numbers for JLCPCB (90% done)
2026-05-04 Stable commit (22 DRC warnings only)
2026-05-04 Added tear drops + tapered tracks
2026-05-04 Added manufacturing files
2026-05-05 BOM consolidation
2026-05-05 Changed L7 to power inductor
2026-05-05 Replaced DTC143ZEBTL with basic parts
2026-05-06 Deleted unneccessary files
2026-05-06 Reorganized datasheets
2026-05-06 First JLCPCB order (Milestone)
2026-05-07 Added README
2026-05-07 Reformatted README
2026-05-08 Small changes
2026-05-08 Added datasheet
